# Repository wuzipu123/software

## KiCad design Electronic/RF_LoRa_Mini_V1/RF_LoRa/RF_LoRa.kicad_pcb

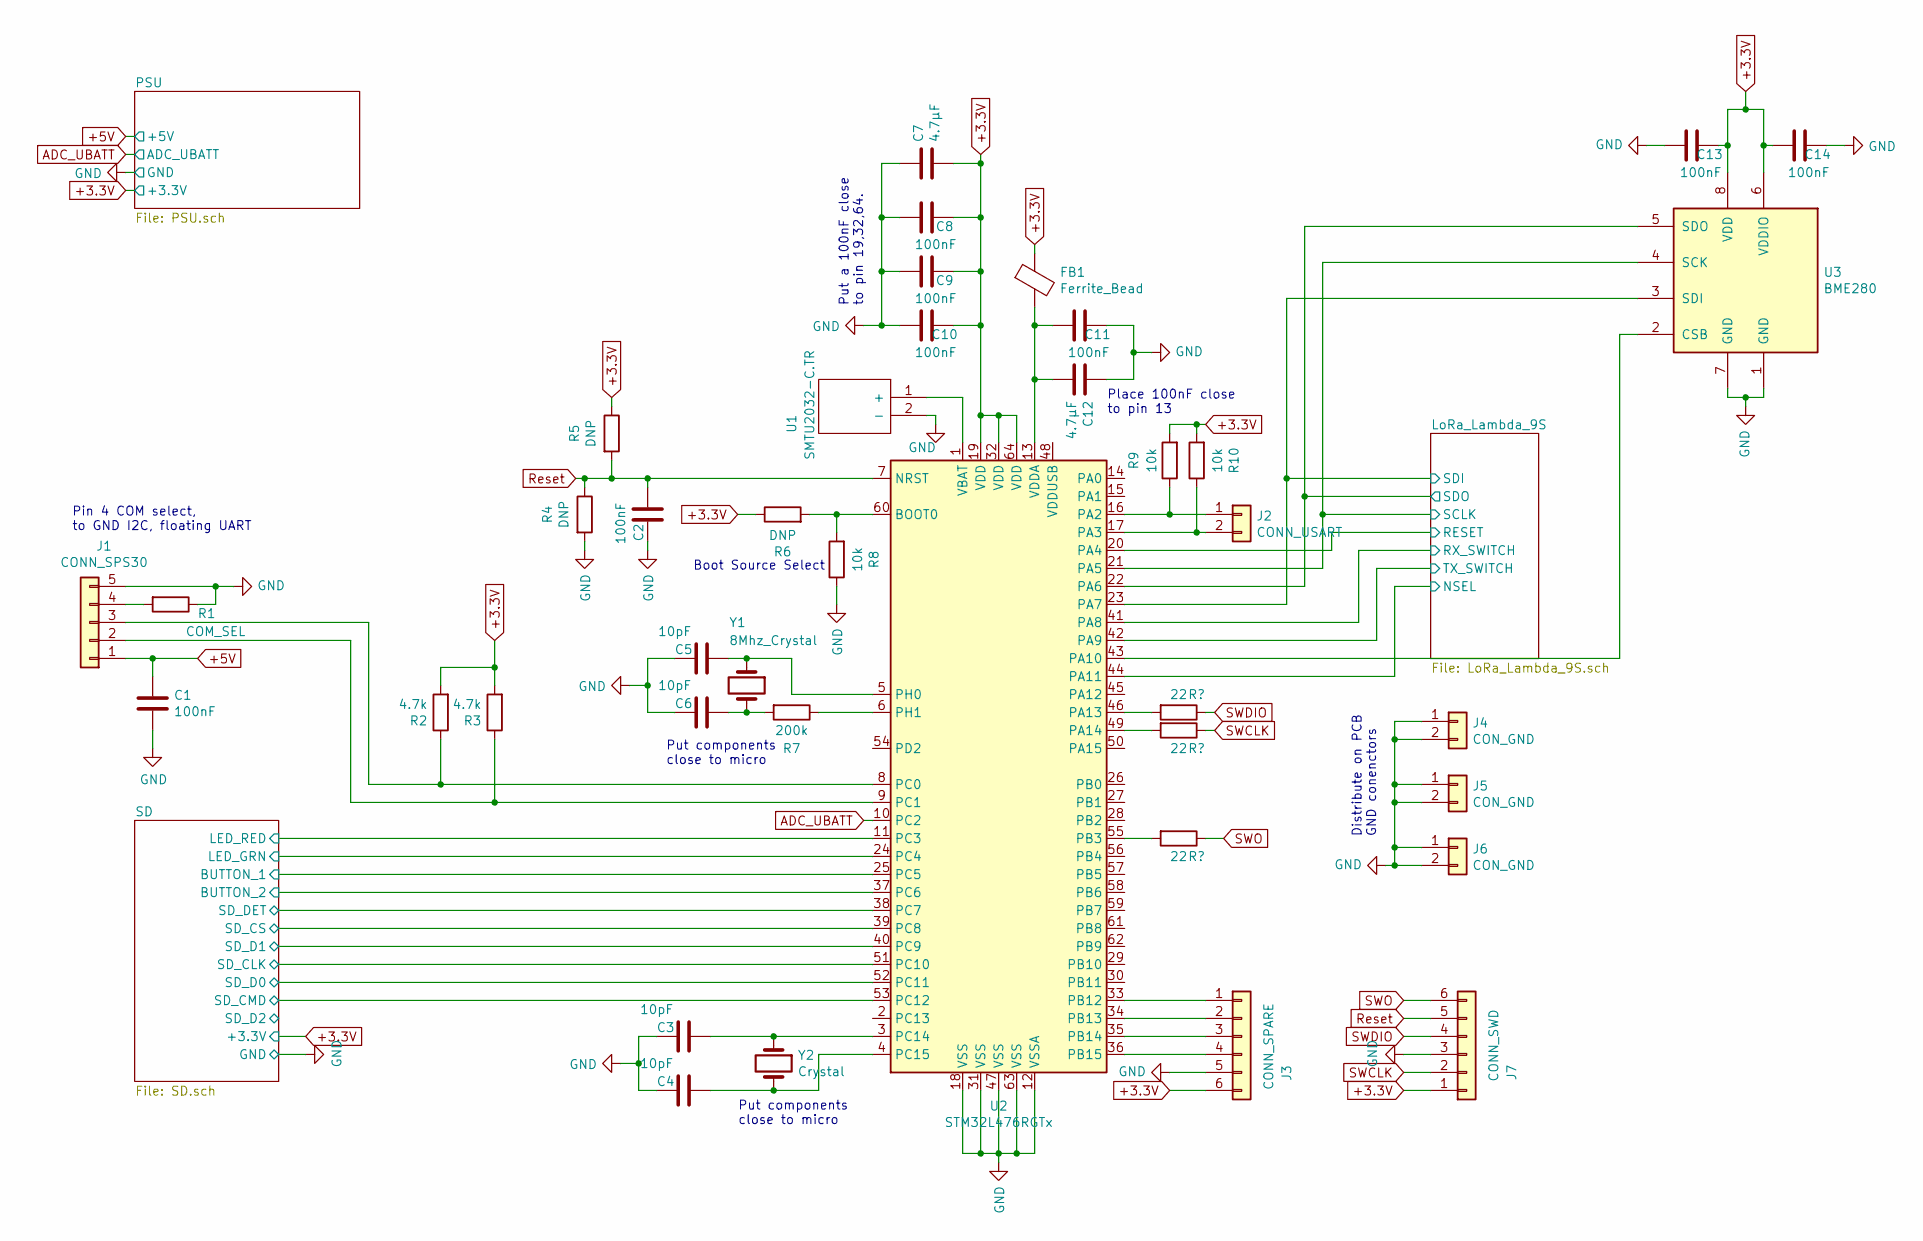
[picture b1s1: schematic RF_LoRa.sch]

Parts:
C1: 100nF; C_0201_0603Metric
C2, C8, C9, C10, C11, C13, C14: 100nF; C_0603_1608Metric
C3, C4, C5, C6: 10pF; C_0603_1608Metric
C7: 4.7µF; R_0201_0603Metric
C12: 4.7µF; C_0805_2012Metric
FB1: Ferrite_Bead; L_0201_0603Metric
J1: CONN_SPS30; JST_XH_B05B-XH-A_1x05_P2.50mm_Vertical
J2: CONN_USART; JST_XH_B02B-XH-A_1x02_P2.50mm_Vertical
J3: CONN_SPARE; JST_XH_B06B-XH-A_1x06_P2.50mm_Vertical
J4, J5, J6: CON_GND; JST_XH_B02B-XH-A_1x02_P2.50mm_Vertical
J7: CONN_SWD; JST_XH_B06B-XH-A_1x06_P2.50mm_Vertical
R1: COM_SEL; R_0603_1608Metric
R2, R3: 4.7k; R_0603_1608Metric
R4, R5, R6: DNP; R_0603_1608Metric
R7: 200k; R_0603_1608Metric
R8, R9, R10: 10k; R_0603_1608Metric
U1: SMTU2032-C.TR; SMTU2032CTR; Mouser Part Number 614-SMTU2032-C.TR
U2: STM32L476RGTx; LQFP-64_10x10mm_P0.5mm
U3: BME280; Bosch_LGA-8_2.5x2.5mm_P0.65mm_ClockwisePinNumbering
Y1: 8Mhz_Crystal; Crystal_SMD_0603-2Pin_6.0x3.5mm_HandSoldering
Y2: Crystal; Crystal_SMD_0603-2Pin_6.0x3.5mm_HandSoldering

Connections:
+3.3V: C7.1, C8.2, C9.2, C10.2, C13.2, C14.1, FB1.1, J3.6, J7.1, R2.2, R3.2, R5.1, R6.1, R9.2, R10.2, U2.19 (VDD), U2.32 (VDD), U2.64 (VDD), U3.6 (VDDIO), U3.8 (VDD); also elsewhere on the board
+5V: C1.1, J1.1; also elsewhere on the board
/LoRa_Lambda_9S/NSEL: U2.44 (PA11); also elsewhere on the board
/LoRa_Lambda_9S/RESET: U2.20 (PA4); also elsewhere on the board
/LoRa_Lambda_9S/RX_SWITCH: U2.41 (PA8); also elsewhere on the board
/LoRa_Lambda_9S/SCLK: U2.21 (PA5), U3.4 (SCK); also elsewhere on the board
/LoRa_Lambda_9S/SDI: U2.23 (PA7), U3.3 (SDI); also elsewhere on the board
/LoRa_Lambda_9S/SDO: U2.22 (PA6), U3.5 (SDO); also elsewhere on the board
/LoRa_Lambda_9S/TX_SWITCH: U2.42 (PA9); also elsewhere on the board
/SD/BUTTON_1: U2.25 (PC5); also elsewhere on the board
/SD/BUTTON_2: U2.37 (PC6); also elsewhere on the board
/SD/LED_GRN: U2.24 (PC4); also elsewhere on the board
/SD/LED_RED: U2.11 (PC3); also elsewhere on the board
/SD/SD_CLK: U2.51 (PC10); also elsewhere on the board
/SD/SD_CMD: U2.53 (PC12); also elsewhere on the board
/SD/SD_CS: U2.39 (PC8); also elsewhere on the board
/SD/SD_D0: U2.52 (PC11); also elsewhere on the board
/SD/SD_D1: U2.40 (PC9); also elsewhere on the board
/SD/SD_DET: U2.38 (PC7); also elsewhere on the board
ADC_UBATT: U2.10 (PC2); also elsewhere on the board
GND: C1.2, C2.2, C3.2, C4.2, C5.2, C6.2, C7.2, C8.1, C9.1, C10.1, C11.2, C12.2, C13.1, C14.2, J1.5, J3.5, J4.1, J4.2, J5.1, J5.2, J6.1, J6.2, J7.3, R1.1, R4.2, R8.1, U1.2 (-), U2.12 (VSSA), U2.18 (VSS), U2.31 (VSS), U2.47 (VSS), U2.63 (VSS), U3.1 (GND), U3.7 (GND); also elsewhere on the board
unnamed: C3.1, U2.3 (PC14), Y2.1
unnamed: C4.1, U2.4 (PC15), Y2.2
unnamed: C5.1, U2.5 (PH0), Y1.1
unnamed: C6.1, R7.2, Y1.2
unnamed: C11.1, C12.1, FB1.2, U2.13 (VDDA)
unnamed: J1.2, R3.1, U2.9 (PC1)
unnamed: J1.3, R2.1, U2.8 (PC0)
unnamed: J1.4, R1.2
unnamed: J2.1, R9.1, U2.16 (PA2)
unnamed: J2.2, R10.1, U2.17 (PA3)
unnamed: J3.1, U2.33 (PB12)
unnamed: J3.2, U2.34 (PB13)
unnamed: J3.3, U2.35 (PB14)
unnamed: J3.4, U2.36 (PB15)
unnamed: R6.2, R8.2, U2.60 (BOOT0)
unnamed: R7.1, U2.6 (PH1)
unnamed 53: U2.46 (PA13); also elsewhere on the board
unnamed 54: U2.49 (PA14); also elsewhere on the board
unnamed 55: U2.55 (PB3); also elsewhere on the board
unnamed: U1.1 (+), U2.1 (VBAT)
unnamed: U2.43 (PA10), U3.2 (CSB)
Reset: C2.1, J7.5, R4.1, R5.2, U2.7 (NRST)
SWCLK: J7.2; also elsewhere on the board
SWDIO: J7.4; also elsewhere on the board
SWO: J7.6; also elsewhere on the board

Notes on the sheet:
Put a 100nF close to pin 19,32,64.
Put components close to micro
Boot Source Select
Place 100nF close to pin 13
Distribute on PCB GND conenctors
Pin 4 COM select, to GND I2C, floating UART

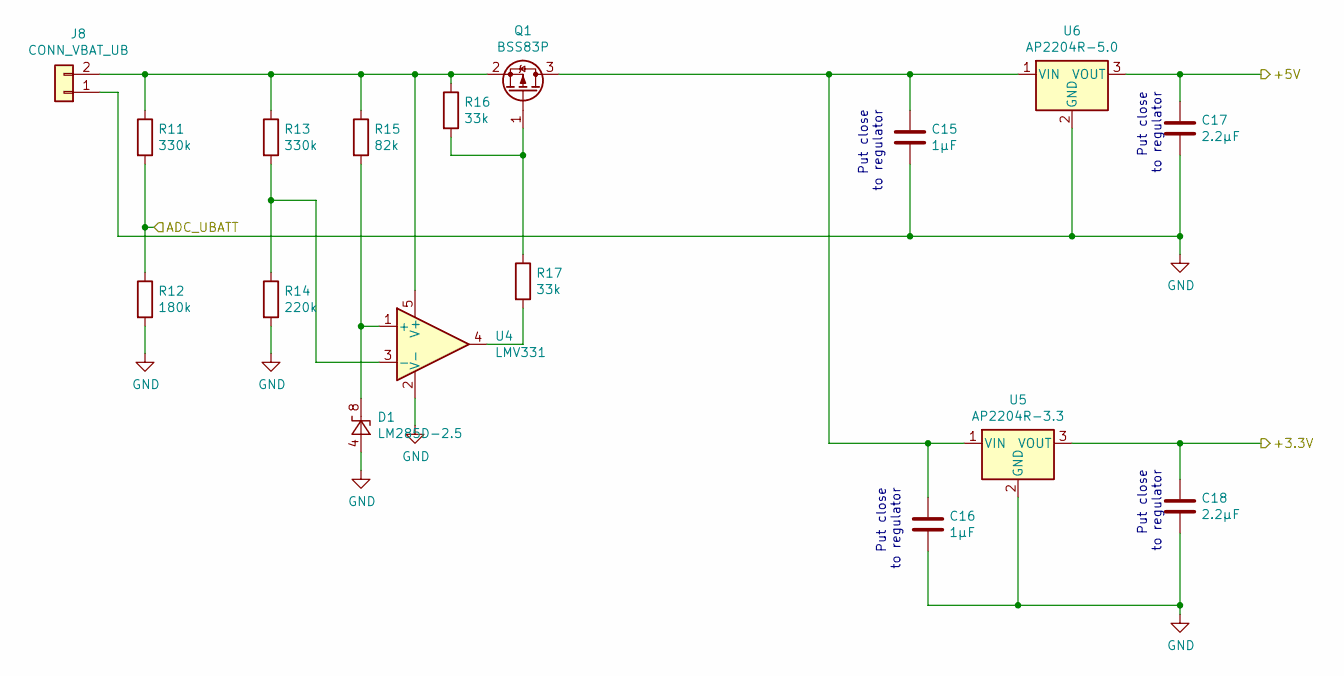
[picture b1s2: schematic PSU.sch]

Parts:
C15, C16: 1µF; C_0603_1608Metric
C17, C18: 2.2µF; C_0603_1608Metric
D1: LM285D-2.5; SOIC-8_3.9x4.9mm_P1.27mm
J8: CONN_VBAT_UB; JST_XH_B02B-XH-A_1x02_P2.50mm_Vertical
Q1: BSS83P; SOT-23
R11, R13: 330k; R_0603_1608Metric
R12: 180k; R_0603_1608Metric
R14: 220k; R_0603_1608Metric
R15: 82k; R_0603_1608Metric
R16, R17: 33k; R_0603_1608Metric
U4: LMV331; SOT-23-5_HandSoldering
U5: AP2204R-3.3; SOT-89-3
U6: AP2204R-5.0; SOT-89-3

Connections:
+3.3V: C18.1, U5.3 (VOUT); also elsewhere on the board
+5V: C17.1, U6.3 (VOUT); also elsewhere on the board
ADC_UBATT: R11.2, R12.1; also elsewhere on the board
GND: C15.2, C16.2, C17.2, C18.2, D1.4 (A), J8.1, R12.2, R14.2, U4.2 (V-), U5.2 (GND), U6.2 (GND); also elsewhere on the board
unnamed: C15.1, C16.1, Q1.3 (D), U5.1 (VIN), U6.1 (VIN)
unnamed: D1.8 (K), R15.2, U4.1 (+)
unnamed: J8.2, Q1.2 (S), R11.1, R13.1, R15.1, R16.1, U4.5 (V+)
unnamed: Q1.1 (G), R16.2, R17.1
unnamed: R13.2, R14.1, U4.3 (-)
unnamed: R17.2, U4.4

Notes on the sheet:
Put close to regulator
Put close to regulator

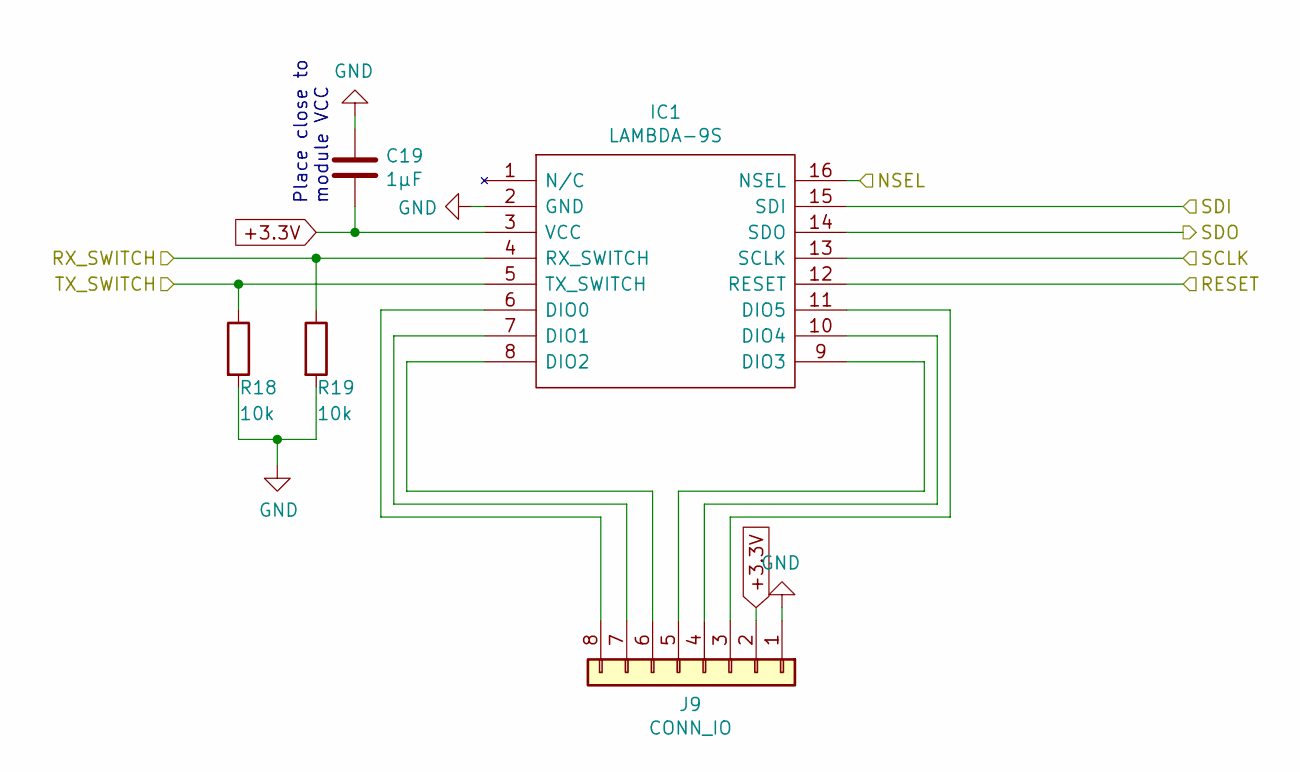
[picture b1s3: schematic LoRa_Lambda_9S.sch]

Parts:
C19: 1µF; C_0603_1608Metric
IC1: LAMBDA-9S; LAMBDA9S; Mouser Part Number 223-LAMBDA-9S
J9: CONN_IO; JST_XH_B08B-XH-A_1x08_P2.50mm_Vertical
R18, R19: 10k; R_0603_1608Metric

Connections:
+3.3V: C19.2, IC1.3 (VCC), J9.2; also elsewhere on the board
/LoRa_Lambda_9S/NSEL: IC1.16 (NSEL); also elsewhere on the board
/LoRa_Lambda_9S/RESET: IC1.12 (RESET); also elsewhere on the board
/LoRa_Lambda_9S/RX_SWITCH: IC1.4 (RX_SWITCH), R19.1; also elsewhere on the board
/LoRa_Lambda_9S/SCLK: IC1.13 (SCLK); also elsewhere on the board
/LoRa_Lambda_9S/SDI: IC1.15 (SDI); also elsewhere on the board
/LoRa_Lambda_9S/SDO: IC1.14 (SDO); also elsewhere on the board
/LoRa_Lambda_9S/TX_SWITCH: IC1.5 (TX_SWITCH), R18.1; also elsewhere on the board
GND: C19.1, IC1.2 (GND), J9.1, R18.2, R19.2; also elsewhere on the board
unnamed: IC1.6 (DIO0), J9.8
unnamed: IC1.7 (DIO1), J9.7
unnamed: IC1.8 (DIO2), J9.6
unnamed: IC1.9 (DIO3), J9.5
unnamed: IC1.10 (DIO4), J9.4
unnamed: IC1.11 (DIO5), J9.3

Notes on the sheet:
Place close to module VCC

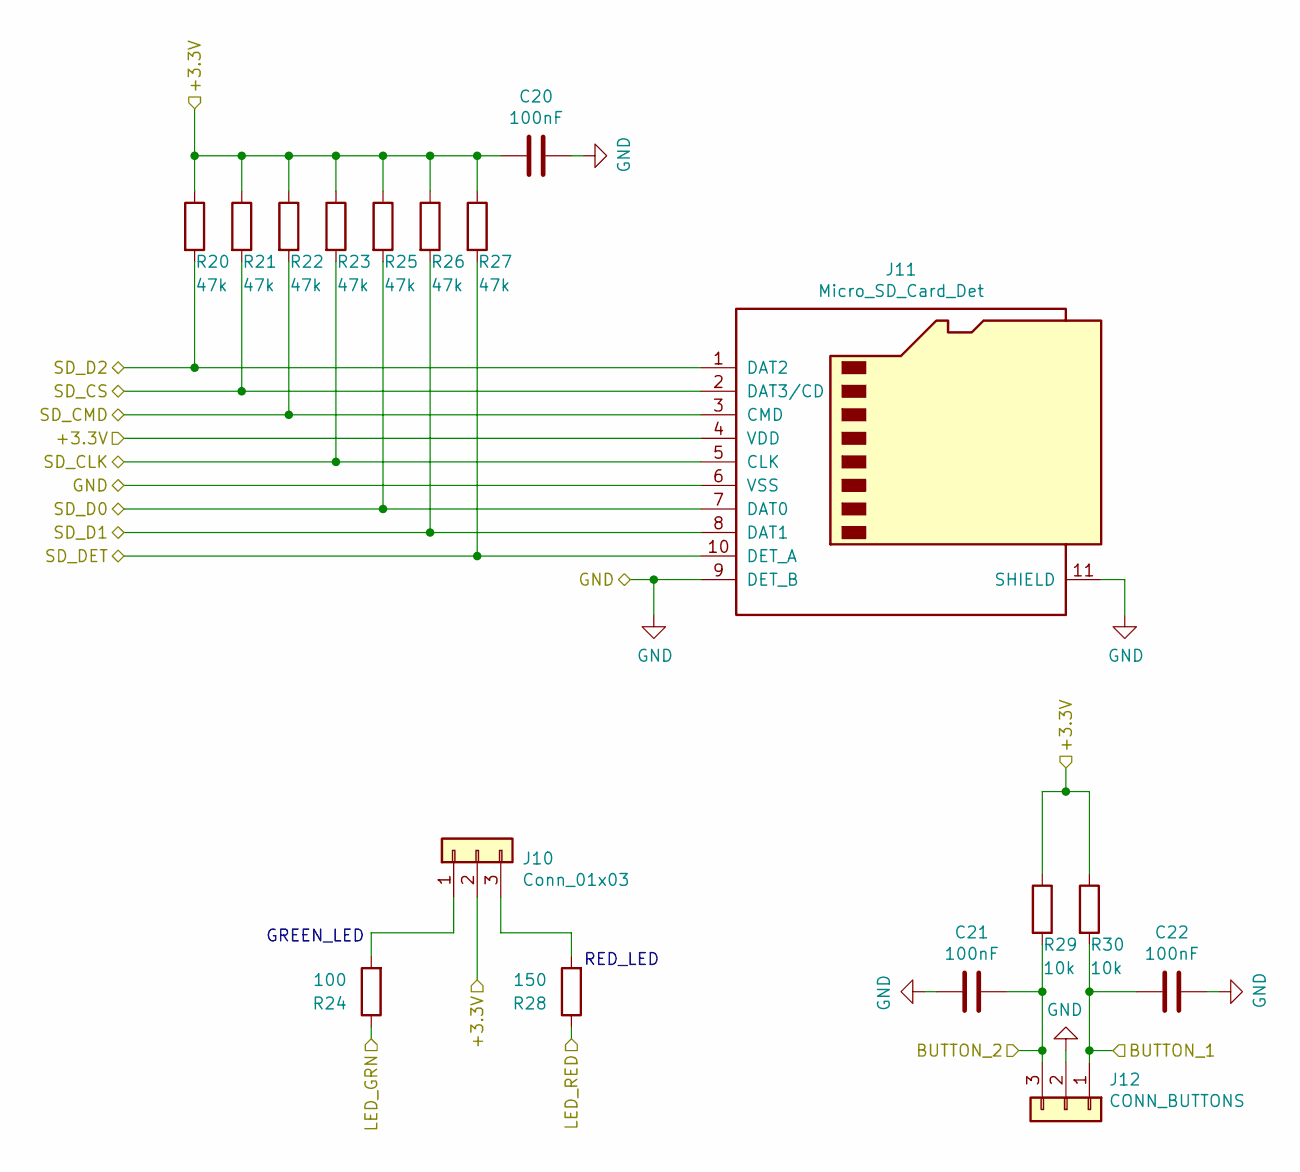
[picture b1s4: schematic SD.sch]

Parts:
C20, C21, C22: 100nF; C_0201_0603Metric
J10: Conn_01x03; JST_XH_B03B-XH-AM_1x03_P2.50mm_Vertical
J11: Micro_SD_Card_Det; microSD_HC_Hirose_DM3AT-SF-PEJM5
J12: CONN_BUTTONS; JST_XH_B03B-XH-A_1x03_P2.50mm_Vertical
R20, R21, R22, R23, R25, R26, R27: 47k; R_0603_1608Metric
R24: 100; R_0603_1608Metric
R28: 150; R_0603_1608Metric
R29, R30: 10k; R_0603_1608Metric

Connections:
+3.3V: C20.2, J10.2, J11.4 (VDD), R20.1, R21.1, R22.1, R23.1, R25.1, R26.1, R27.1, R29.1, R30.1; also elsewhere on the board
/SD/BUTTON_1: C22.2, J12.1, R30.2; also elsewhere on the board
/SD/BUTTON_2: C21.1, J12.3, R29.2; also elsewhere on the board
/SD/LED_GRN: R24.1; also elsewhere on the board
/SD/LED_RED: R28.1; also elsewhere on the board
/SD/SD_CLK: J11.5 (CLK), R23.2; also elsewhere on the board
/SD/SD_CMD: J11.3 (CMD), R22.2; also elsewhere on the board
/SD/SD_CS: J11.2 (DAT3/CD), R21.2; also elsewhere on the board
/SD/SD_D0: J11.7 (DAT0), R25.2; also elsewhere on the board
/SD/SD_D1: J11.8 (DAT1), R26.2; also elsewhere on the board
/SD/SD_D2: J11.1 (DAT2), R20.2
/SD/SD_DET: J11.10 (DET_A), R27.2; also elsewhere on the board
GND: C20.1, C21.2, C22.1, J11.6 (VSS), J11.9 (DET_B), J11.11 (SHIELD), J12.2; also elsewhere on the board
unnamed: J10.1, R24.2
unnamed: J10.3, R28.2

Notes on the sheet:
RED_LED
GREEN_LED

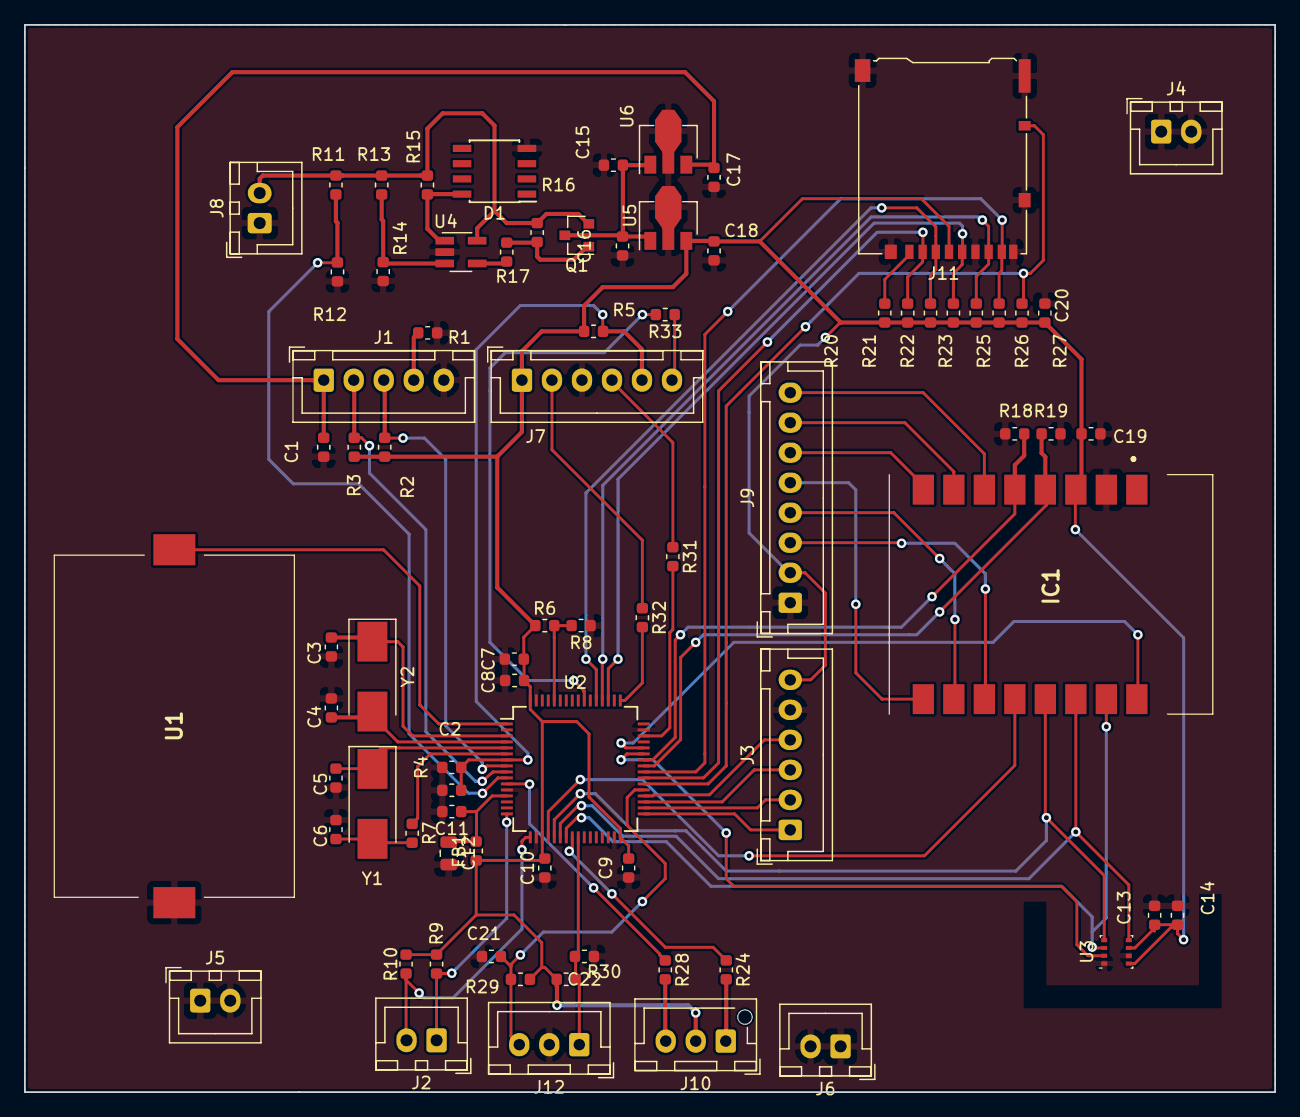
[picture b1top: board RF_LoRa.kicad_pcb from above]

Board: 2 copper layers, 104.1 x 88.9 mm, 79 parts (0 on the bottom side), 61 nets.

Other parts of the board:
R31, R32, R33: 22; R_0603_1608Metric

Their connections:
unnamed 53: R31.2; also elsewhere on the board
unnamed 54: R32.2; also elsewhere on the board
unnamed 55: R33.2; also elsewhere on the board
SWCLK: R32.1; also elsewhere on the board
SWDIO: R31.1; also elsewhere on the board
SWO: R33.1; also elsewhere on the board

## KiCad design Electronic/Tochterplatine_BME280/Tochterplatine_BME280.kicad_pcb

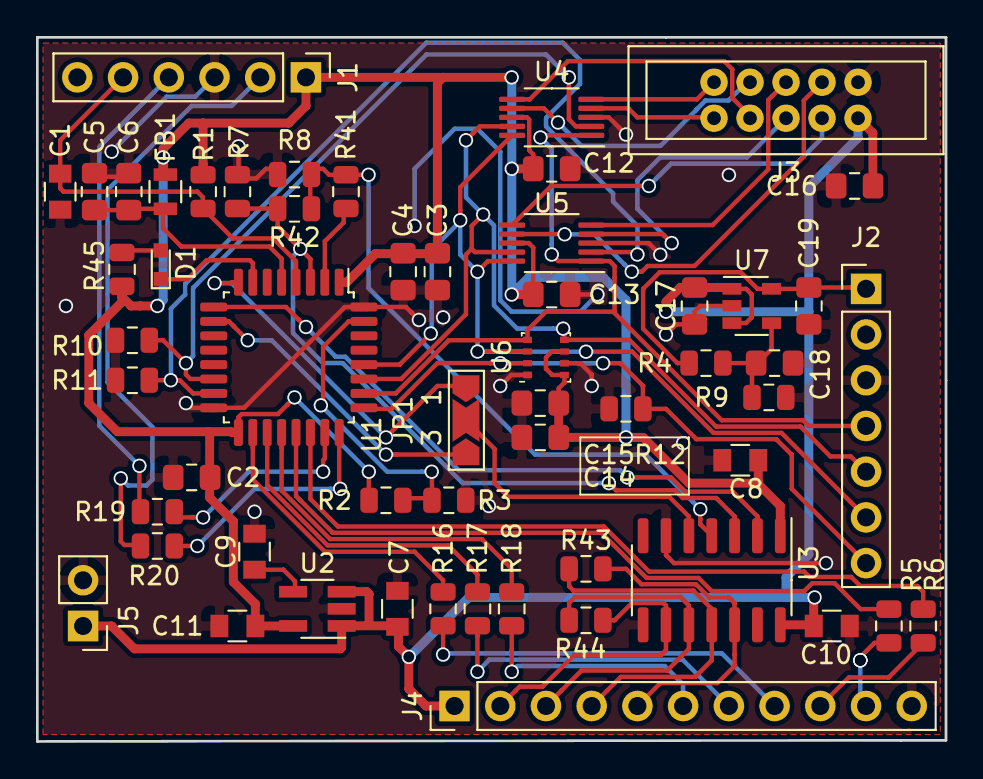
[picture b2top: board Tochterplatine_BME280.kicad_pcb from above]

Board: 2 copper layers, 50.5 x 39.1 mm, 56 parts (0 on the bottom side), 50 nets.

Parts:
C1, C8, C10: 100n; C_0805
C2, C3, C5, C12, C13, C14, C15, C16, C17: 100n; C_0805_2012Metric_Pad1.15x1.40mm_HandSolder
C4, C6: 1u; C_0805_2012Metric_Pad1.15x1.40mm_HandSolder
C7, C11: 1u; C_0805
C9: 10n; C_0805
C18: 470pF; C_0805_2012Metric_Pad1.15x1.40mm_HandSolder
C19: 2.2uF; C_0805_2012Metric_Pad1.15x1.40mm_HandSolder
D1: LED; LED_0603
FB1: Ferrite_Bead; L_0805
J1: Conn_01x06_Male; PinHeader_1x06_P2.54mm_Vertical
J2: Conn_01x07; PinHeader_1x07_P2.54mm_Vertical
J3: Conn_02x05_Row_Letter_First; TOBYA05
J4: Conn_01x11; PinHeader_1x11_P2.54mm_Vertical
J5: Conn_01x02; PinHeader_1x02_P2.54mm_Vertical
JP1: SolderJumper_3_Open; SolderJumper-3_P2.0mm_Open_TrianglePad1.0x1.5mm_NumberLabels
R1, R2, R7, R41, R42: DNP; R_0805_2012Metric
R3, R8, R10, R11, R12: 10k; R_0805_2012Metric
R4: 360k; R_0805_2012Metric
R5, R6, R19, R20: 22R; R_0805_2012Metric
R9: 180k; R_0805_2012Metric
R16, R17, R18: 100R; R_0805_2012Metric
R43, R44: 120R; R_0805_2012Metric
R45: 480R; R_0805_2012Metric
U1: STM32L021K4Tx; LQFP-32_7x7mm_P0.8mm
U2: LDK130-33_SOT23_SOT353; SOT-23-5_HandSoldering
U3: MAX13432EESD; SOIC-14_3.9x8.7mm_P1.27mm
U4, U5: ADS1118IDGS; VSSOP-10_3x3mm_P0.5mm
U6: BME280; Bosch_LGA-8_2.5x2.5mm_P0.65mm_ClockwisePinNumbering
U7: MIC5205YM5; SOT-23-5

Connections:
+3V3: C2.1, C3.1, C4.1, C8.2, C11.2, C12.1, C13.1, C14.1, C15.1, FB1.1, J1.1, R1.1, R2.1, R45.1, U1.1, U1.17, U2.5, U3.1, U4.8, U5.8, U6.6, U6.8
+5V: C7.2, C10.1, C16.1, C17.1, J3.a5, J4.1, J5.1, U2.1, U2.3, U3.14, U7.1, U7.3
/3.8V: C19.1, J2.1, R4.2, U7.5
/AIN0_0: J3.a1, U4.4
/AIN0_1: J3.a3, U5.4
/AIN1_0: J3.b1, U4.5
/AIN1_1: J3.b3, U5.5
/AIN2_0: J3.a2, U4.6
/AIN2_1: J3.a4, U5.6
/AIN3_0: J3.b2, U4.7
/AIN3_1: J3.b4, U5.7
/Adr0: J4.8, R16.1
/Adr1: J4.7, R17.1
/Adr2: J4.6, R18.1
/CP0: J4.10, R5.2
/CP1: J4.9, R6.2
/LPUART1_TX_STM32L021: JP1.3, U1.10
/Main_Connection/RS485_A: J4.2, R44.1, U3.9
/Main_Connection/RS485_B: J4.3, R44.2, U3.10
/Main_Connection/RS485_Y: J4.5, R43.1, U3.12
/Main_Connection/RS485_Z: J4.4, R43.2, U3.11
/NRST: C1.1, J1.5, R1.2, U1.4
/SPI_MISO: J2.5, U1.27, U4.9, U5.9, U6.5
/SPI_MOSI: J2.6, U1.28, U4.10, U5.10, U6.3
/SPI_NSS_ADC_1: R10.1, U1.14, U4.2
/SPI_NSS_ADC_2: R11.1, U1.15, U5.2
/SPI_NSS_BME280: J2.7, R12.1, U1.25, U6.2
/SPI_SCK: J2.4, U1.26, U4.1, U5.1, U6.4
/SWCLK: J1.2, R20.1
/SWDIO: J1.4, R19.1
/UART_DE: R7.1, R42.1, U1.3, U3.3
/UART_RE: R41.1, U1.2
/UART_RX: U1.9, U3.2
/UART_TX: JP1.2, U3.5
/USART2_TX_STM32L051: JP1.1, U1.8
GND: C1.2, C2.2, C3.2, C4.2, C5.2, C6.2, C7.1, C8.1, C9.1, C10.2, C11.1, C12.2, C13.2, C14.2, C15.2, C16.2, C17.2, C18.2, C19.2, J1.3, J2.3, J3.b5, J4.11, J5.2, R3.2, R7.2, R8.2, R9.2, R10.2, R11.2, R12.2, U1.16, U1.32, U2.2, U3.6, U3.8, U4.3, U5.3, U6.1, U6.7, U7.2
unnamed: C5.1, C6.1, FB1.2, U1.5
unnamed: C9.2, U2.4
unnamed: C18.1, R4.1, R9.1, U7.4
unnamed: D1.1, U1.7
unnamed: D1.2, R45.2
unnamed: R2.2, R3.1, U1.31
unnamed: R5.1, U1.21
unnamed: R6.1, U1.22
unnamed: R16.2, U1.18
unnamed: R17.2, U1.19
unnamed: R18.2, U1.20
unnamed: R19.2, U1.23
unnamed: R20.2, U1.24
unnamed: R8.1, R41.2, R42.2, U3.4

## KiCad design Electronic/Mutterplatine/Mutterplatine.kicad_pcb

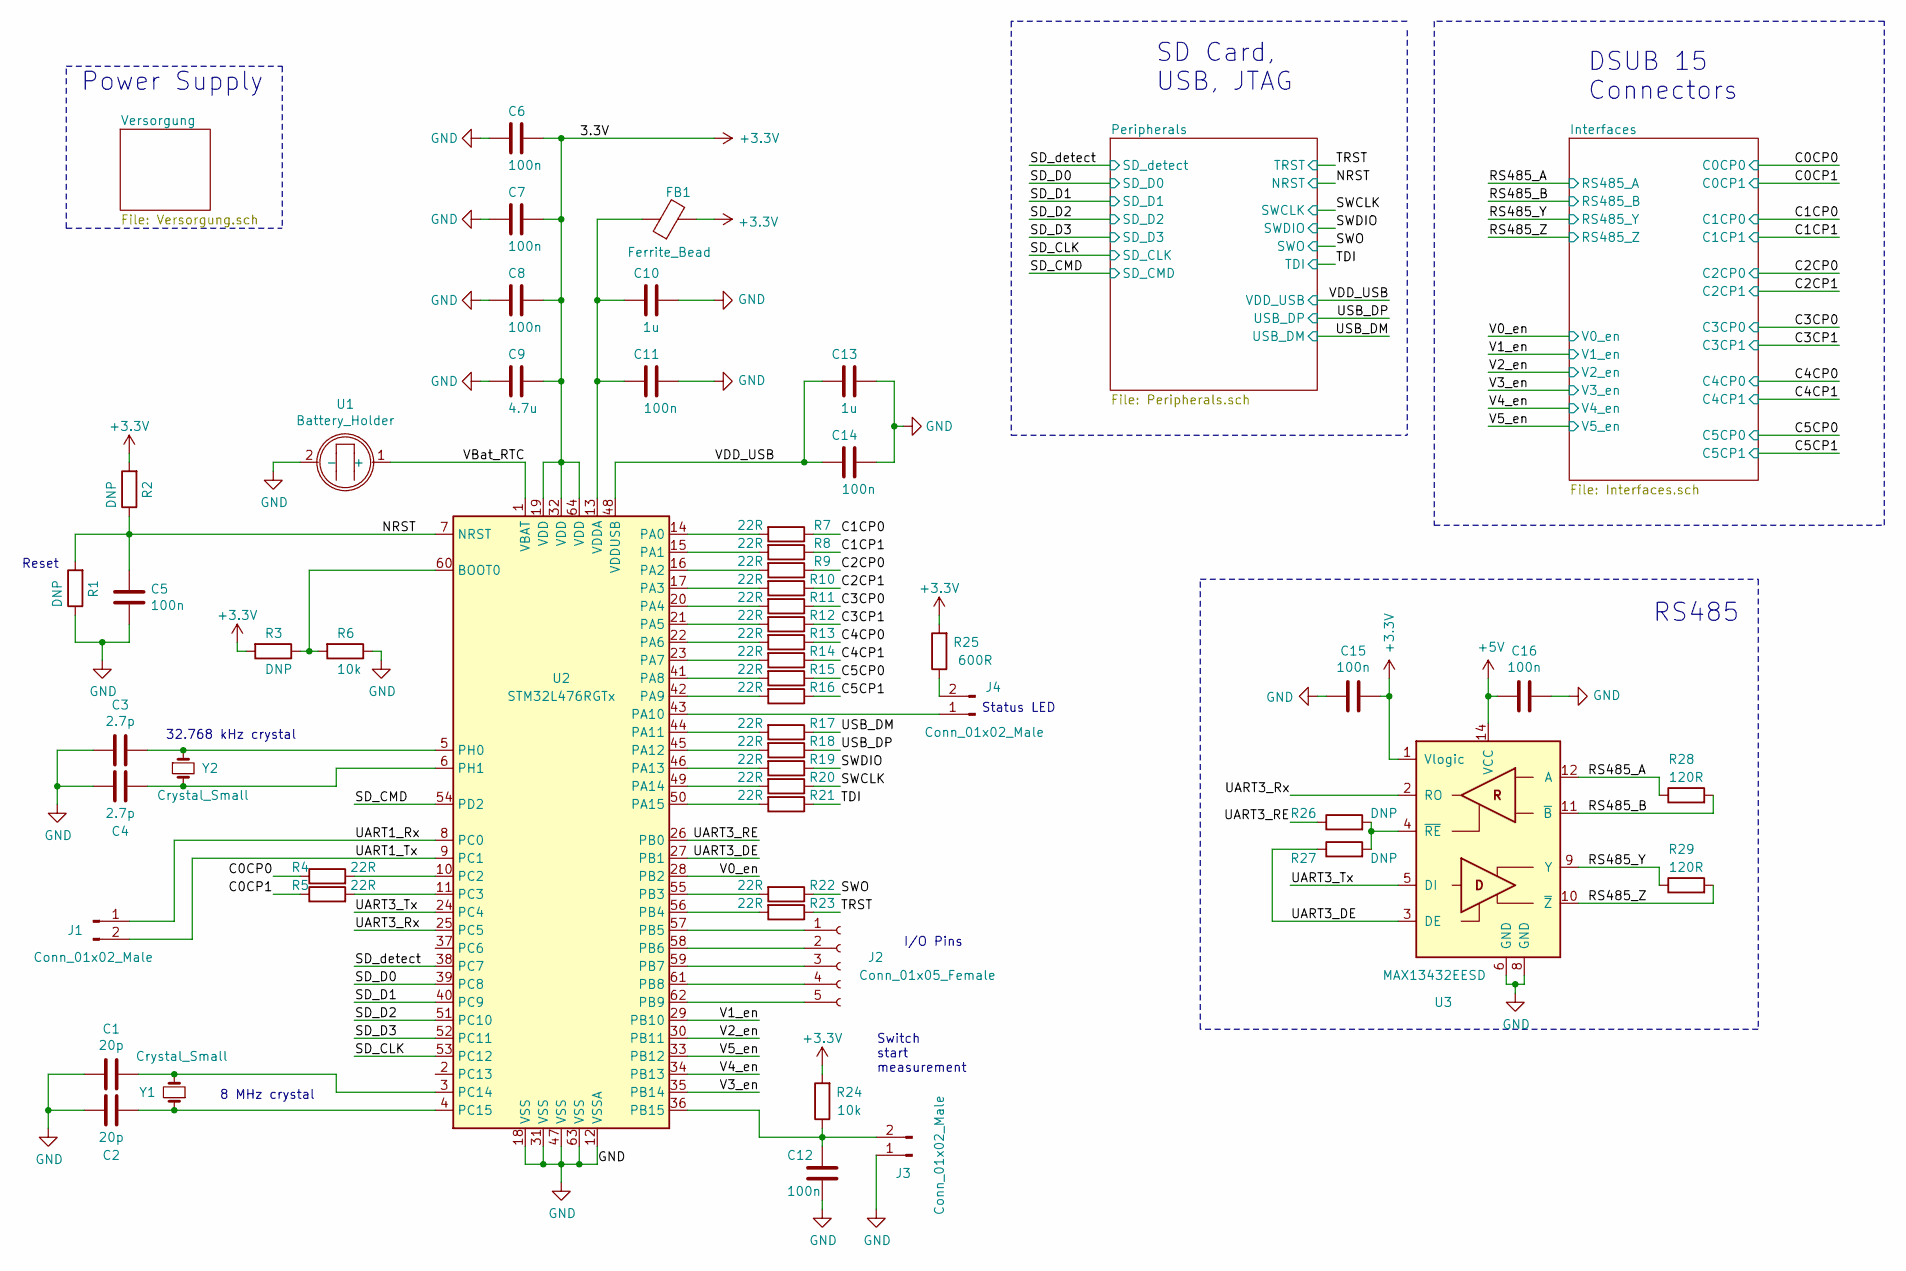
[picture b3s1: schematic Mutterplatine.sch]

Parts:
C1, C2: 20p; C_0805_2012Metric_Pad1.15x1.40mm_HandSolder
C3, C4: 2.7p; C_0805_2012Metric_Pad1.15x1.40mm_HandSolder
C5, C6, C7, C8, C11, C12, C14, C15, C16: 100n; C_0805_2012Metric_Pad1.15x1.40mm_HandSolder
C9: 4.7u; C_0805_2012Metric_Pad1.15x1.40mm_HandSolder
C10, C13: 1u; C_0805_2012Metric_Pad1.15x1.40mm_HandSolder
FB1: Ferrite_Bead; L_0805_2012Metric_Pad1.15x1.40mm_HandSolder
J1, J3, J4: Conn_01x02_Male; PinHeader_1x02_P2.54mm_Vertical
J2: Conn_01x05_Female; PinSocket_1x05_P2.54mm_Vertical
R1, R2, R3, R26, R27: DNP; R_0805_2012Metric_Pad1.15x1.40mm_HandSolder
R4, R5, R7, R8, R9, R10, R11, R12, R13, R14, R15, R16, R17, R18, R19, R20, R21, R22, R23: 22R; R_0805_2012Metric_Pad1.15x1.40mm_HandSolder
R6, R24: 10k; R_0805_2012Metric_Pad1.15x1.40mm_HandSolder
R25: 600R; R_0805_2012Metric_Pad1.15x1.40mm_HandSolder
R28, R29: 120R; R_0805_2012Metric_Pad1.15x1.40mm_HandSolder
U1: Battery_Holder; BatteryHolder_Keystone_1060_1x2032
U2: STM32L476RGTx; LQFP-64_10x10mm_P0.5mm
U3: MAX13432EESD; SOIC-14_3.9x8.7mm_P1.27mm
Y1: Crystal_Small; Crystal_SMD_3225-4Pin_3.2x2.5mm_HandSoldering
Y2: Crystal_Small; Crystal_SMD_2012-2Pin_2.0x1.2mm_HandSoldering

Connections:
+3V3: C6.2, C7.2, C8.2, C9.2, C15.2, FB1.2, R2.2, R3.2, R24.2, R25.2, U2.19 (VDD), U2.32 (VDD), U2.64 (VDD), U3.1 (Vlogic); also elsewhere on the board
+5V: C16.1, U3.14 (VCC); also elsewhere on the board
/C0CP0: R4.1; also elsewhere on the board
/C0CP1: R5.1; also elsewhere on the board
/C1CP1: R8.1; also elsewhere on the board
/C2CP1: R10.1; also elsewhere on the board
/C3CP0: R11.1; also elsewhere on the board
/C3CP1: R12.1; also elsewhere on the board
/C4CP0: R13.1; also elsewhere on the board
/C4CP1: R14.1; also elsewhere on the board
/C5CP0: R15.1; also elsewhere on the board
/C5CP1: R16.1; also elsewhere on the board
/NRST: C5.1, R1.2, R2.1, U2.7 (NRST); also elsewhere on the board
/RS485_A: R28.1, U3.12 (A); also elsewhere on the board
/RS485_B: R28.2, U3.11 (~B); also elsewhere on the board
/RS485_Y: R29.1, U3.9 (Y); also elsewhere on the board
/RS485_Z: R29.2, U3.10 (~Z~); also elsewhere on the board
/SD_CLK: U2.53 (PC12); also elsewhere on the board
/SD_CMD: U2.54 (PD2); also elsewhere on the board
/SD_D0: U2.39 (PC8); also elsewhere on the board
/SD_D1: U2.40 (PC9); also elsewhere on the board
/SD_D2: U2.51 (PC10); also elsewhere on the board
/SD_D3: U2.52 (PC11); also elsewhere on the board
/SD_detect: U2.38 (PC7); also elsewhere on the board
/SWCLK: R20.1; also elsewhere on the board
/SWDIO: R19.1; also elsewhere on the board
/SWO: R22.1; also elsewhere on the board
/TDI: R21.1; also elsewhere on the board
/TRST: R23.1; also elsewhere on the board
/UART1_Rx: J1.1, U2.8 (PC0)
/UART1_Tx: J1.2, U2.9 (PC1)
/UART3_DE: R27.1, U2.27 (PB1), U3.3 (DE)
/UART3_RE: R26.1, U2.26 (PB0)
/UART3_Rx: U2.25 (PC5), U3.2 (RO)
/UART3_Tx: U2.24 (PC4), U3.5 (DI)
/USB_DM: R17.1; also elsewhere on the board
/USB_DP: R18.1; also elsewhere on the board
/V0_en: U2.28 (PB2); also elsewhere on the board
/V1_en: U2.29 (PB10); also elsewhere on the board
/V2_en: U2.30 (PB11); also elsewhere on the board
/V3_en: U2.35 (PB14); also elsewhere on the board
/V4_en: U2.34 (PB13); also elsewhere on the board
/V5_en: U2.33 (PB12); also elsewhere on the board
/VBat_RTC: U1.1 (+), U2.1 (VBAT)
/VDD_USB: C13.2, C14.2, U2.48 (VDDUSB); also elsewhere on the board
unnamed: C1.2, U2.3 (PC14), Y1.2
unnamed: C2.2, U2.4 (PC15), Y1.1
unnamed: C3.2, U2.5 (PH0), Y2.1
unnamed: C10.2, C11.2, FB1.1, U2.13 (VDDA)
unnamed: C12.1, J3.2, R24.1, U2.36 (PB15)
unnamed: J2.1, U2.57 (PB5)
unnamed: J2.2, U2.58 (PB6)
unnamed: J2.3, U2.59 (PB7)
unnamed: J2.4, U2.61 (PB8)
unnamed: J2.5, U2.62 (PB9)
unnamed: J4.1, U2.43 (PA10)
unnamed: J4.2, R25.1
unnamed: R3.1, R6.2, U2.60 (BOOT0)
unnamed: R4.2, U2.10 (PC2)
unnamed: R5.2, U2.11 (PC3)
unnamed: R8.2, U2.15 (PA1)
unnamed: R10.2, U2.17 (PA3)
unnamed: R11.2, U2.20 (PA4)
unnamed: R12.2, U2.21 (PA5)
unnamed: R13.2, U2.22 (PA6)
unnamed: R14.2, U2.23 (PA7)
unnamed: R15.2, U2.41 (PA8)
unnamed: R16.2, U2.42 (PA9)
unnamed: R17.2, U2.44 (PA11)
unnamed: R18.2, U2.45 (PA12)
unnamed: R19.2, U2.46 (PA13)
unnamed: R20.2, U2.49 (PA14)
unnamed: R21.2, U2.50 (PA15)
unnamed: R22.2, U2.55 (PB3)
unnamed: R23.2, U2.56 (PB4)
unnamed: R26.2, R27.2, U3.4 (~RE)

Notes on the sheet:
32.768 kHz crystal
8 MHz crystal
Reset
RS485
DSUB 15 Connectors
SD Card, USB, JTAG
Power Supply
Status LED
Switch start measurement
I/O Pins

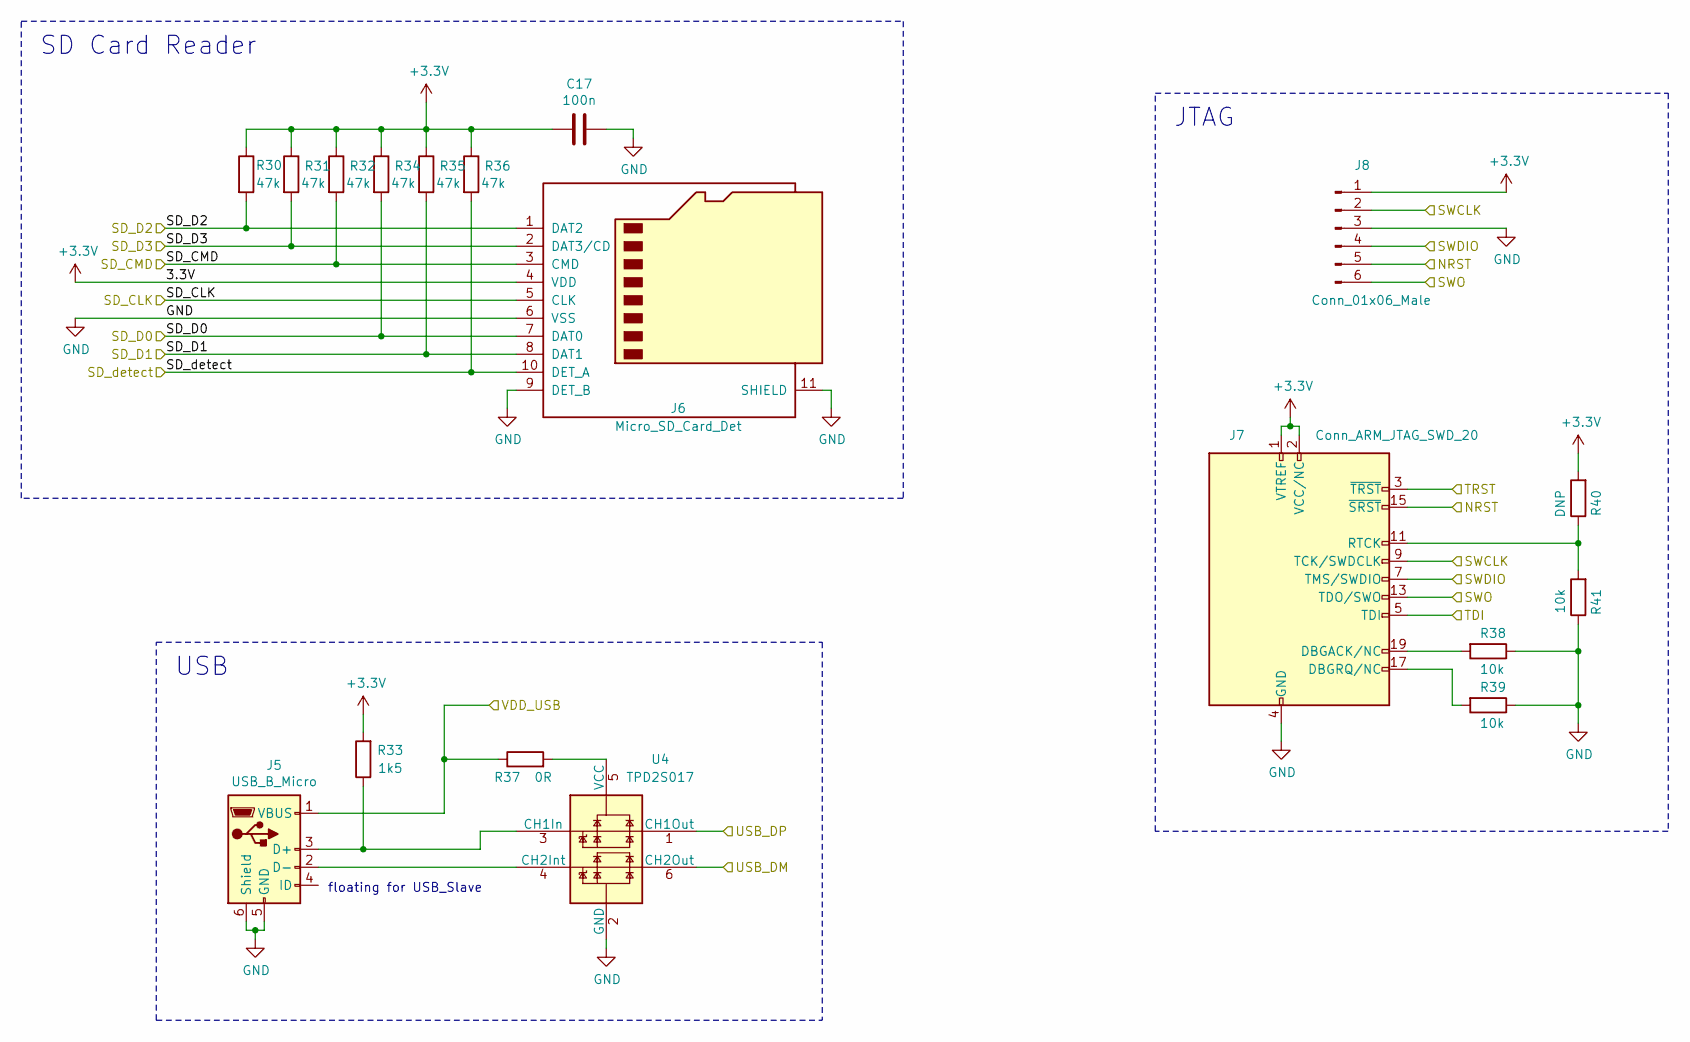
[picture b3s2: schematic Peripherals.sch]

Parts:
C17: 100n; C_0805_2012Metric_Pad1.15x1.40mm_HandSolder
J5: USB_B_Micro; USB_Micro-B_GCT_USB3076-30-A
J6: Micro_SD_Card_Det; microSD_HC_Hirose_DM3D-SF
J7: Conn_ARM_JTAG_SWD_20; PinHeader_2x10_P2.54mm_Vertical
J8: Conn_01x06_Male; PinHeader_1x06_P2.54mm_Vertical
R30, R31, R32, R34, R35, R36: 47k; R_0805_2012Metric_Pad1.15x1.40mm_HandSolder
R33: 1k5; R_0805_2012Metric_Pad1.15x1.40mm_HandSolder
R37: 0R; R_0805_2012Metric_Pad1.15x1.40mm_HandSolder
R38, R39, R41: 10k; R_0805_2012Metric_Pad1.15x1.40mm_HandSolder
R40: DNP; R_0805_2012Metric_Pad1.15x1.40mm_HandSolder
U4: TPD2S017; SOT-23-6

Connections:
+3V3: C17.2, J6.4 (VDD), J7.1 (VTREF), J7.2 (VCC/NC), J8.1, R30.1, R31.1, R32.1, R33.2, R34.1, R35.1, R36.1, R40.2; also elsewhere on the board
/NRST: J7.15 (~SRST~), J8.5; also elsewhere on the board
/SD_CLK: J6.5 (CLK); also elsewhere on the board
/SD_CMD: J6.3 (CMD), R32.2; also elsewhere on the board
/SD_D0: J6.7 (DAT0), R34.2; also elsewhere on the board
/SD_D1: J6.8 (DAT1), R35.2; also elsewhere on the board
/SD_D2: J6.1 (DAT2), R30.2; also elsewhere on the board
/SD_D3: J6.2 (DAT3/CD), R31.2; also elsewhere on the board
/SD_detect: J6.10 (DET_A), R36.2; also elsewhere on the board
/SWCLK: J7.9 (TCK/SWDCLK), J8.2; also elsewhere on the board
/SWDIO: J7.7 (TMS/SWDIO), J8.4; also elsewhere on the board
/SWO: J7.13 (TDO/SWO), J8.6; also elsewhere on the board
/TDI: J7.5 (TDI); also elsewhere on the board
/TRST: J7.3 (~TRST~); also elsewhere on the board
/USB_DM: U4.6 (CH2Out); also elsewhere on the board
/USB_DP: U4.1 (CH1Out); also elsewhere on the board
/VDD_USB: J5.1 (VBUS), R37.1; also elsewhere on the board
unnamed: J5.2 (D-), U4.4 (CH2Int)
unnamed: J5.3 (D+), R33.1, U4.3 (CH1In)
unnamed: J7.11 (RTCK), R40.1, R41.2
unnamed: J7.17 (DBGRQ/NC), R39.2
unnamed: J7.19 (DBGACK/NC), R38.2
unnamed: R37.2, U4.5 (VCC)

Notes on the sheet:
floating for USB_Slave
SD Card Reader
JTAG
USB
